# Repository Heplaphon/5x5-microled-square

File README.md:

# Microled square
A small square with a 5x5 led matrix.  
Front side pcb has footprint for a seeed xiao esp32s3m and backside holds the 5x5 ws2812b 1010 led matrix.  
This was made on an evening to try and learn KiCad.

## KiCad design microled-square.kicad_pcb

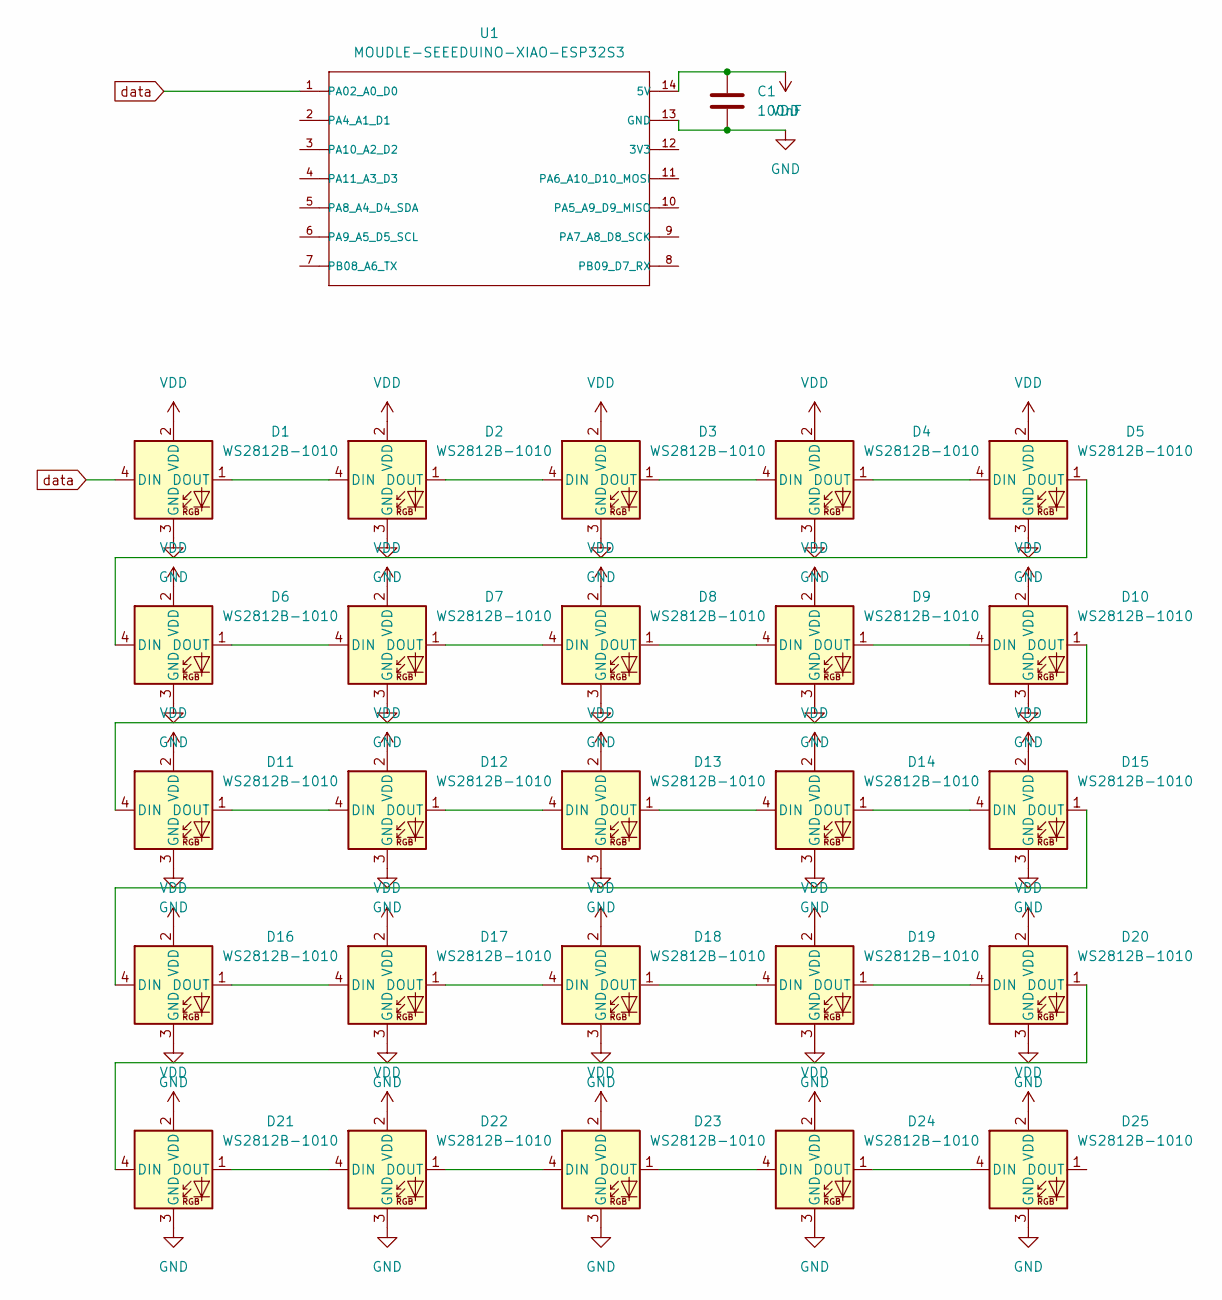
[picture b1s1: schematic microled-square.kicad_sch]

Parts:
C1: 100nF
D1, D2, D3, D4, D5, D6, D7, D8, D9, D10, D11, D12, D13, D14, D15, D16, D17, D18, D19, D20, D21, D22, D23, D24, D25: WS2812B-1010; LED_WS2812B-2020_PLCC4_2.0x2.0mm
U1: MOUDLE-SEEEDUINO-XIAO-ESP32S3; MOUDLE14P-SMD-2.54-21X17.8MM

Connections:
GND: C1.2, D1.3 (GND), D2.3 (GND), D3.3 (GND), D4.3 (GND), D5.3 (GND), D6.3 (GND), D7.3 (GND), D8.3 (GND), D9.3 (GND), D10.3 (GND), D11.3 (GND), D12.3 (GND), D13.3 (GND), D14.3 (GND), D15.3 (GND), D16.3 (GND), D17.3 (GND), D18.3 (GND), D19.3 (GND), D20.3 (GND), D21.3 (GND), D22.3 (GND), D23.3 (GND), D24.3 (GND), D25.3 (GND), U1.13 (GND)
unnamed: D1.1 (DOUT), D2.4 (DIN)
unnamed: D2.1 (DOUT), D3.4 (DIN)
unnamed: D3.1 (DOUT), D4.4 (DIN)
unnamed: D4.1 (DOUT), D5.4 (DIN)
unnamed: D5.1 (DOUT), D6.4 (DIN)
unnamed: D6.1 (DOUT), D7.4 (DIN)
unnamed: D7.1 (DOUT), D8.4 (DIN)
unnamed: D8.1 (DOUT), D9.4 (DIN)
unnamed: D9.1 (DOUT), D10.4 (DIN)
unnamed: D10.1 (DOUT), D11.4 (DIN)
unnamed: D11.1 (DOUT), D12.4 (DIN)
unnamed: D12.1 (DOUT), D13.4 (DIN)
unnamed: D13.1 (DOUT), D14.4 (DIN)
unnamed: D14.1 (DOUT), D15.4 (DIN)
unnamed: D15.1 (DOUT), D16.4 (DIN)
unnamed: D16.1 (DOUT), D17.4 (DIN)
unnamed: D17.1 (DOUT), D18.4 (DIN)
unnamed: D18.1 (DOUT), D19.4 (DIN)
unnamed: D19.1 (DOUT), D20.4 (DIN)
unnamed: D20.1 (DOUT), D21.4 (DIN)
unnamed: D21.1 (DOUT), D22.4 (DIN)
unnamed: D22.1 (DOUT), D23.4 (DIN)
unnamed: D23.1 (DOUT), D24.4 (DIN)
unnamed: D24.1 (DOUT), D25.4 (DIN)
VDD: C1.1, D1.2 (VDD), D2.2 (VDD), D3.2 (VDD), D4.2 (VDD), D5.2 (VDD), D6.2 (VDD), D7.2 (VDD), D8.2 (VDD), D9.2 (VDD), D10.2 (VDD), D11.2 (VDD), D12.2 (VDD), D13.2 (VDD), D14.2 (VDD), D15.2 (VDD), D16.2 (VDD), D17.2 (VDD), D18.2 (VDD), D19.2 (VDD), D20.2 (VDD), D21.2 (VDD), D22.2 (VDD), D23.2 (VDD), D24.2 (VDD), D25.2 (VDD), U1.14 (5V)
data: D1.4 (DIN), U1.1 (PA02_A0_D0)

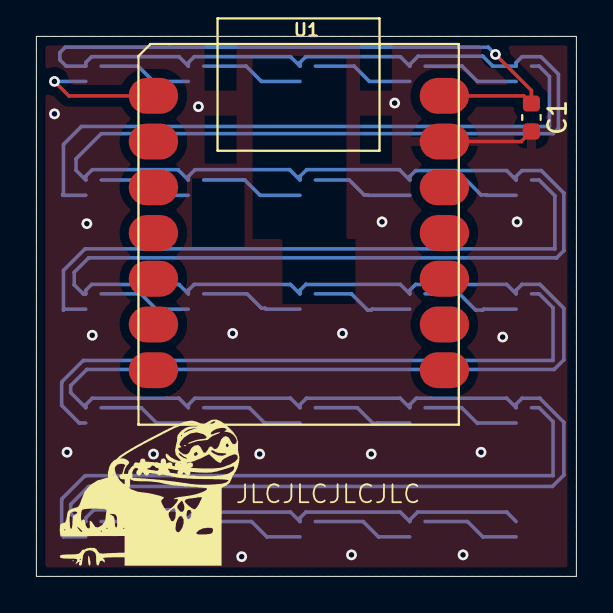
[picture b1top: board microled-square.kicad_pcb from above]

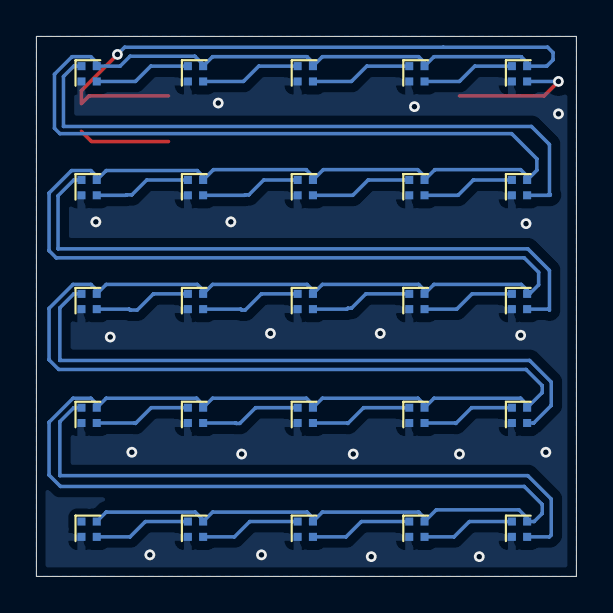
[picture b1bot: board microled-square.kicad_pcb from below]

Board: 2 copper layers, 30.0 x 30.0 mm, 27 parts (25 on the bottom side), 27 nets.

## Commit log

2024-05-21 push schematics to git
2024-05-21 remove old project file
2024-05-28 fix: can't just rename files, renamed back LED footprint
